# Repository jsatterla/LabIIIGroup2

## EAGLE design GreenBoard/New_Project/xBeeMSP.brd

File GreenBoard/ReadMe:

## this file is of no importance. However, the green board files contained within this are slighly. lol

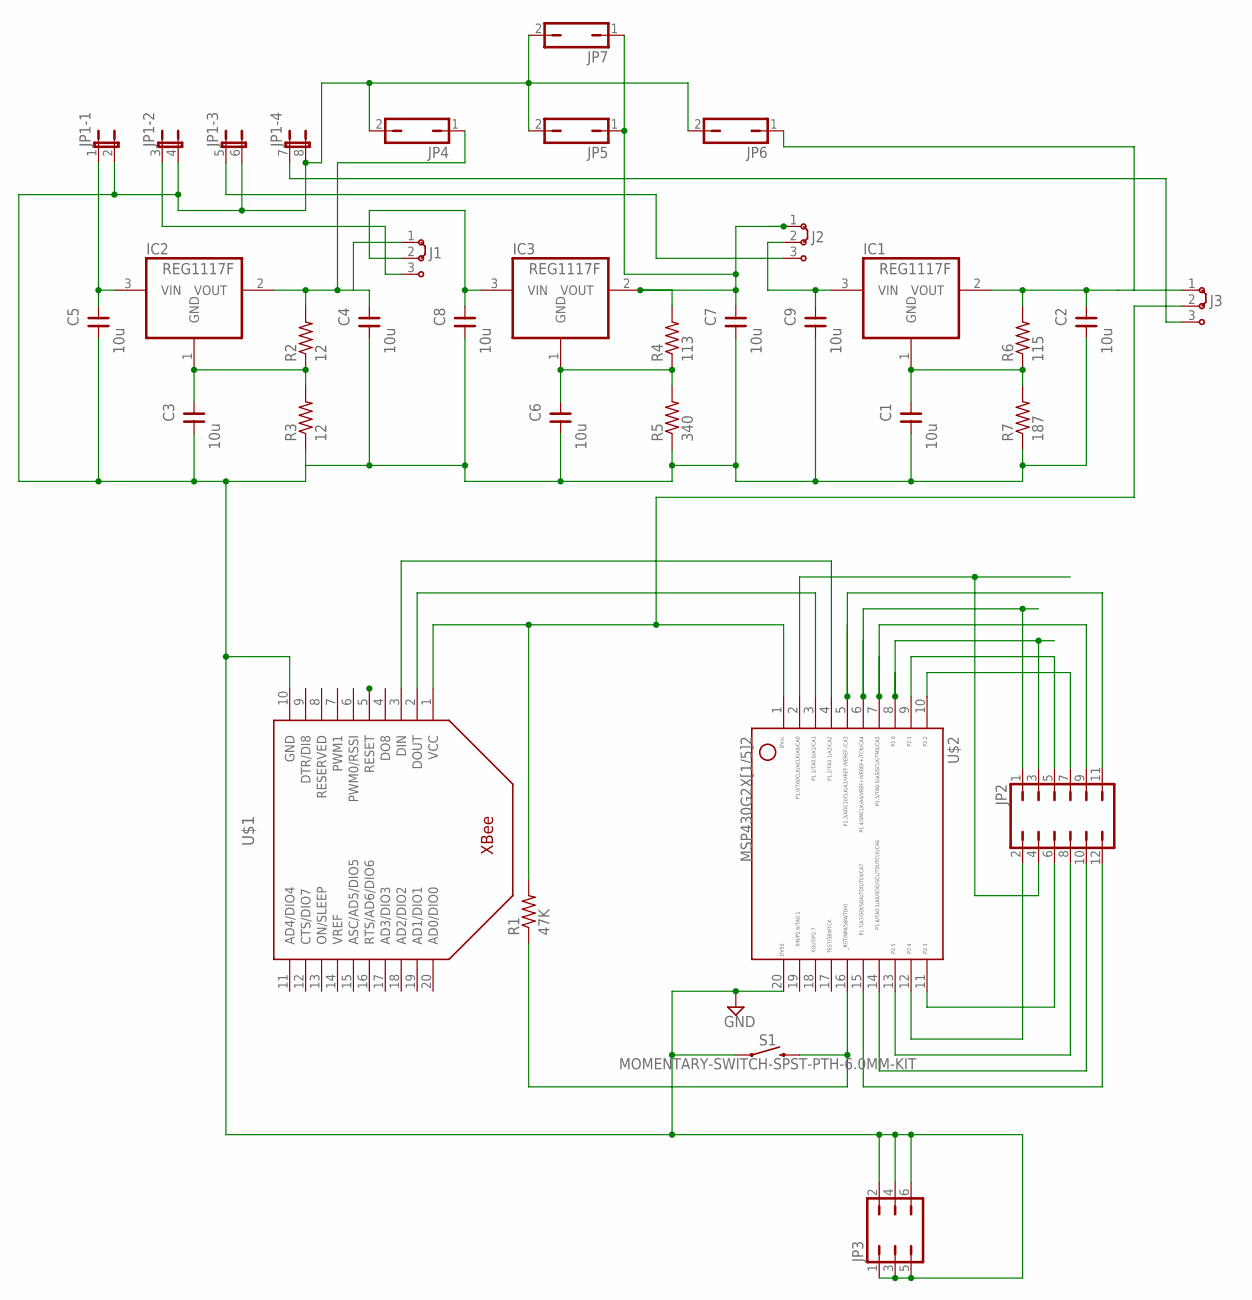
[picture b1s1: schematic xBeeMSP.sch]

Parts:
C1, C2, C3, C4, C5, C6, C7, C8, C9: 10u; C020-035X018
IC1, IC2, IC3: REG1117F; DD-3
J1, J2, J3: J2X2MM; 04C
JP1: JP4QE; JP4Q
JP2: JP6Q
JP3: JP3Q
JP4, JP5, JP6, JP7: JP1Q; JP1
R1: 47K; 0207/10
R2, R3: 12; 0207/10
R4: 113; 0207/10
R5: 340; 0207/10
R6: 115; 0207/10
R7: 187; 0207/10
S1: MOMENTARY-SWITCH-SPST-PTH-6.0MM-KIT; TACTILE_SWITCH_PTH_6.0MM_KIT
U$1: XBEE
U$2: G2X[1/5]2---N20; N20

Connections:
3.3VOUT: C2.2, IC1.2 (VOUT), J3.1, JP6.1, R6.2
5VIN: C9.2, IC1.3 (VIN), J2.2
5VOUT: C7.2, IC3.2 (VOUT), J2.1, JP5.1, JP7.1, R4.2
12VIN: C8.2, IC3.3 (VIN), J1.2
12VOUT: C4.2, IC2.2 (VOUT), J1.1, JP4.1, R2.2
BACKUP-5VIN: J2.3, JP1.5 (1)
BACKUP-12VIN: J1.3, JP1.3 (1)
BACKUP-VCC: J3.3, JP1.7 (1)
GND: C1.1, C2.1, C3.1, C4.1, C5.1, C6.1, C7.1, C8.1, C9.1, JP1.2, JP1.4 (2), JP1.6 (2), JP1.8 (2), JP3.1, JP3.2, JP3.3, JP3.4, JP3.5, JP3.6, JP4.2, JP5.2, JP6.2, JP7.2, R3.1, R5.1, R7.1, S1.1, U$1.5 (RESET), U$1.10 (GND), U$2.20
unnamed: U$1.2 (DOUT), U$2.3
unnamed: U$1.3 (DIN), U$2.4
unnamed: JP2.4, U$2.2
unnamed: R1.1, S1.3 (2), U$2.16
unnamed: JP2.9, U$2.7
unnamed: JP2.3, U$2.8
unnamed: JP2.12, U$2.15
unnamed: JP2.11, U$2.5
unnamed: JP2.5, U$2.9
unnamed: JP2.1, U$2.6
unnamed: JP2.10, U$2.14
unnamed: JP2.7, U$2.10
unnamed: JP2.8, U$2.13
unnamed: JP2.2, U$2.12
unnamed: JP2.6, U$2.11
unnamed: C3.2, IC2.1 (GND), R2.1, R3.2
unnamed: C1.2, IC1.1 (GND), R6.1, R7.2
unnamed: C6.2, IC3.1 (GND), R4.1, R5.2
unnamed: C5.2, IC2.3 (VIN), JP1.1
VCC: J3.2, R1.2, U$1.1 (VCC), U$2.1

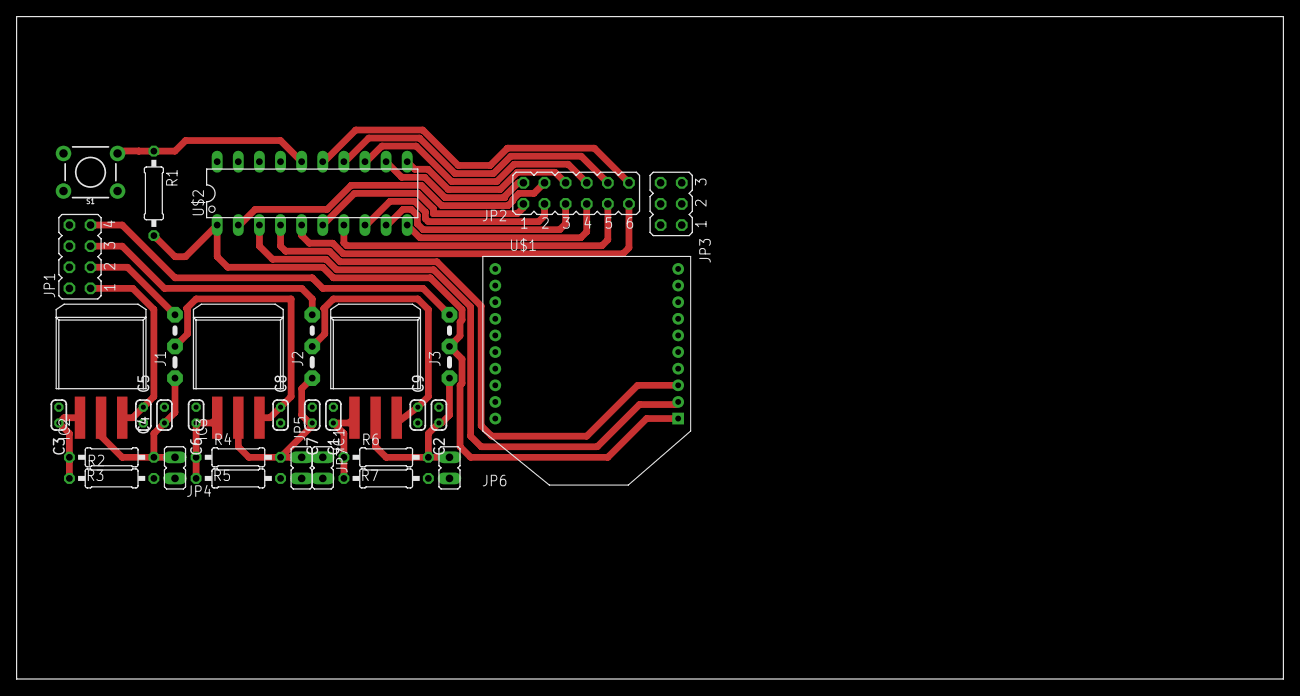
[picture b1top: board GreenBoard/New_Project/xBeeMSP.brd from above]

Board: 2 copper layers, 152.4 x 79.7 mm, 32 parts (0 on the bottom side), 29 nets.

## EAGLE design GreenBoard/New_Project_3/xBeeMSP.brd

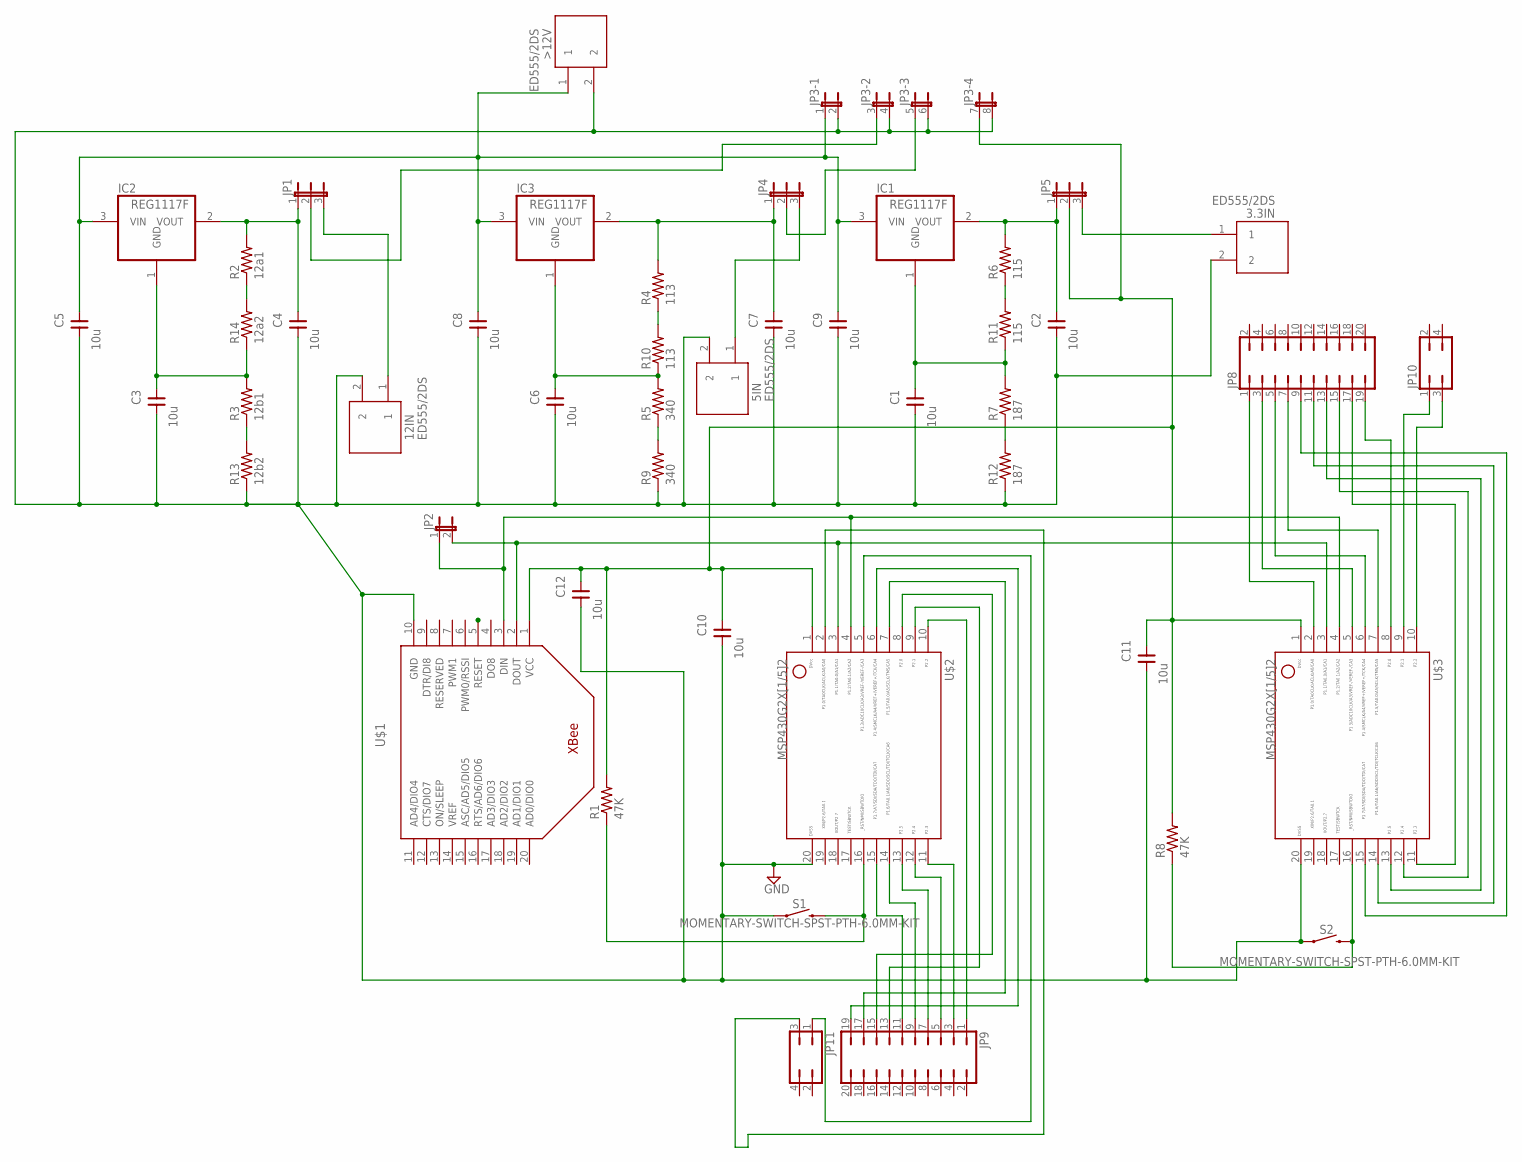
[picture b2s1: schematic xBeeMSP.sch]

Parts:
3.3IN, 5IN, 12IN: ED555/2DS
>12V: ED555/2DS
C1, C2, C3, C4, C5, C6, C7, C8, C9, C10, C11, C12: 10u; C020-035X018
IC1, IC2, IC3: REG1117F; DD-3
JP1, JP4, JP5: JP2E; JP2
JP2: JP1E; JP1
JP3: JP4QE; JP4Q
JP8, JP9: JP10Q
JP10, JP11: JP2Q
R1, R8: 47K; 0207/10
R2: 12a1; 0207/10
R3: 12b1; 0207/10
R4, R10: 113; 0207/10
R5, R9: 340; 0207/10
R6, R11: 115; 0207/10
R7, R12: 187; 0207/10
R13: 12b2; 0207/10
R14: 12a2; 0207/10
S1, S2: MOMENTARY-SWITCH-SPST-PTH-6.0MM-KIT; TACTILE_SWITCH_PTH_6.0MM_KIT
U$1: XBEE
U$2, U$3: G2X[1/5]2---N20; N20

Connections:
3.3VOUT: C2.2, IC1.2 (VOUT), JP5.1, R6.2
5VOUT: C7.2, IC3.2 (VOUT), JP4.1, R4.2
12VOUT: C4.2, IC2.2 (VOUT), JP1.1, R2.2
GND: 3.3IN.2, 5IN.2, 12IN.2, >12V.2, C1.1, C2.1, C3.1, C4.1, C5.1, C6.1, C7.1, C8.1, C9.1, C10.1, C11.1, C12.1, JP3.2, JP3.4 (2), JP3.6 (2), JP3.8 (2), R9.1, R12.1, R13.1, S1.1, S2.1, U$1.5 (RESET), U$1.10 (GND), U$2.20, U$3.20
unnamed: JP2.2, U$1.2 (DOUT), U$2.3, U$3.3
unnamed: JP9.3, U$2.11
unnamed: JP2.1, U$1.3 (DIN), U$2.4, U$3.4
unnamed: R1.1, S1.3 (2), U$2.16
unnamed: JP9.1, U$2.10
unnamed: JP9.13, U$2.9
unnamed: JP9.15, U$2.8
unnamed: JP9.17, U$2.7
unnamed: JP9.5, U$2.12
unnamed: JP9.19, U$2.6
unnamed: JP11.1, U$2.5
unnamed: JP11.3, U$2.2
unnamed: JP9.7, U$2.13
unnamed: JP9.9, U$2.14
unnamed: R8.1, S2.3 (2), U$3.16
unnamed: JP9.11, U$2.15
unnamed: JP8.1, U$3.2
unnamed: JP8.3, U$3.5
unnamed: JP3.5 (1), JP4.2
unnamed: JP8.5, U$3.6
unnamed: R2.1, R14.2
unnamed: JP8.7, U$3.7
unnamed: R4.1, R10.2
unnamed: JP8.17, U$3.11
unnamed: JP8.15, U$3.12
unnamed: C6.2, IC3.1 (GND), R5.2, R10.1
unnamed: JP8.13, U$3.13
unnamed: JP8.11, U$3.14
unnamed: JP8.9, U$3.15
unnamed: R6.1, R11.2
unnamed: R5.1, R9.2
unnamed: C1.2, IC1.1 (GND), R7.2, R11.1
unnamed: R7.1, R12.2
unnamed: C3.2, IC2.1 (GND), R3.2, R14.1
unnamed: 12IN.1, JP1.3
unnamed: R3.1, R13.2
unnamed: 5IN.1, JP4.3
unnamed: JP8.19, U$3.8
unnamed: >12V.1, C5.2, C8.2, C9.2, IC1.3 (VIN), IC2.3 (VIN), IC3.3 (VIN), JP3.1
unnamed: 3.3IN.1, JP5.3
unnamed: JP10.1, U$3.9
unnamed: JP10.3, U$3.10
unnamed: JP1.2, JP3.3 (1)
VCC: C10.2, C11.2, C12.2, JP3.7 (1), JP5.2, R1.2, R8.2, U$1.1 (VCC), U$2.1, U$3.1

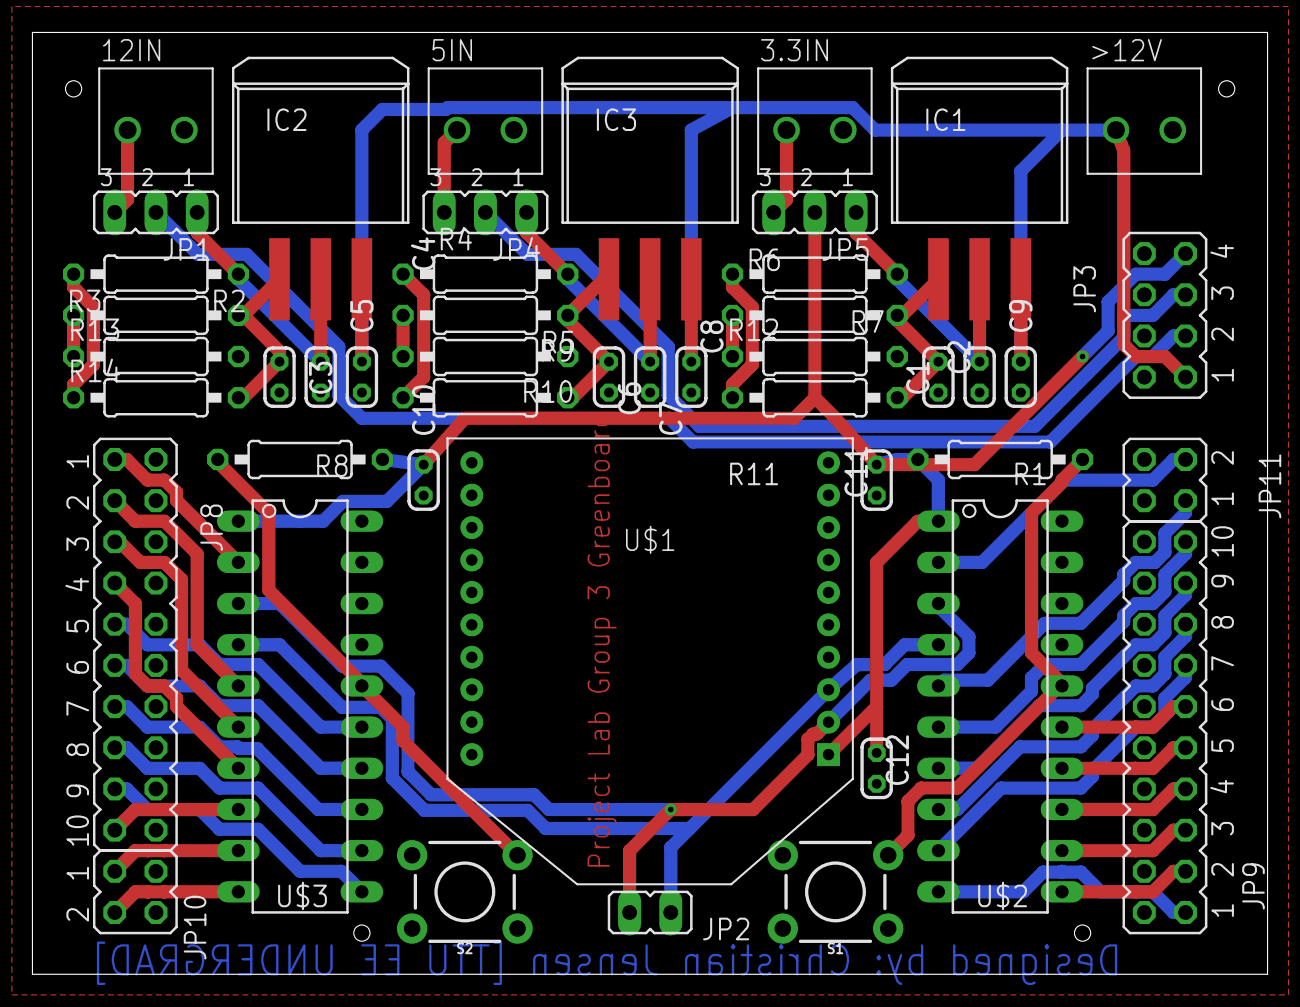
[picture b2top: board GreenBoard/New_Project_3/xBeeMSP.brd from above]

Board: 2 copper layers, 76.2 x 58.1 mm, 47 parts (0 on the bottom side), 48 nets.

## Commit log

2018-10-17 Create Amplifier Datasheets
2018-11-22 Create Precision Amplifier Circuit Notes
2018-11-22 Create Code Updates
2018-11-22 Create NewCCSCode
2018-11-22 Create Python Code
2018-11-22 Create Pulse Oximetry Update
2018-11-28 Create Microcontroller
2018-11-28 Create RN-42 (BlueSMiRF)
2018-12-05 Update V2
    detector.py has been modified to detect authenticated user vs unknown user. It will also send char "A" to Serial Port to send a signal to MSP430G to open the door.
2018-12-05 Stepper Motor and driver datasheet
    SM-42BYG011-25 Bipolar stepper motor is used with the easy driver to move motor upon receiving signal.
2018-12-05 Rename readme.md to READme.md
2018-12-05 Rename Zigbee Network Programs/msp430g2xx3_usci_uart_standard_transceiver.c to Zigbee Network Programs/MSP-1/msp430g2xx3_usci_uart_standard_transceiver.c
2018-12-10 Create ReadMe
    create

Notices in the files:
parts and their libraries:
SparkFun-Switches: Licensing: Creative Commons ShareAlike 4.0 International - https://creativecommons.org/licenses/by-sa/4.0
